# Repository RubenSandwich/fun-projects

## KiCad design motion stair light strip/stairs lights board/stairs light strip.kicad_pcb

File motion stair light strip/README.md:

## motion activated stair light strip

A simple, no IOT, motion activated stair light

## BOM

* 24v power supply
* [Sensky 6A DC 12V 24V PIR Motion Sensor](https://www.amazon.com/Sensky-Function-Control-Controller-Lighting/dp/B0B4K2Q7K9/ref=sr_1_23?crid=3AGQ66JBI1T4I&dib=eyJ2IjoiMSJ9.xUSOzHpblpoWn406B4-OBZFLz6d4soG2-rCj22BZ4TVwtl2oj7zBpFSsm9bGVf4_0vr2__NiO2qRjmIovLB6Cl-oex97yxg1mPl1SFR1d35Xbk69rIP4NijKcqR74HMDt8XPdo_WN_JfRDuOrUlUvaxq_QLUiuyCcHjCWXG1KOQzDuKs777sMJBGEr9q2cRSSDjf5W2F9OwXw6ElvNTGThpiMOUk_iMA_sRr2h6lEkTxdSnYWCXfyEl0XtqK0hp1d54DAIPvzWh6n2200xwKC1Srvh-nk0dEnyT1JrPJjKc.FILWEKSNVr479REpNQmRwOyHtakDh_g0QBcfDnpH2tw&dib_tag=se&keywords=motion%2Bactivated%2Bmodule&qid=1732066020&sprefix=motion%2Bactivated%2Bmodule%2Caps%2C201&sr=8-23&th=1)
* [Light strip](https://www.amazon.com/IKERY-Silicone-Waterproof-Decoration（Power-Included）/dp/B0B7RDBT89/ref=sr_1_22_sspa?crid=3Q7LC3KLRZKES&dib=eyJ2IjoiMSJ9.uvSizN30if3GPO9yVlsrHTzEI6fy9r3d7WXvXWqh24xlPGxJmMbmaGfHv6yVIscbHMaRuJwYZWzsTD4VyLnd_XchH1hdfdvzGfN6ygw8GdbzDVly5eUVatRmDDCMvimbZPNP77smsaMjOpAMJSRxJzvhMKM2c1lFD6wII6Rla-b9U_iaw8UnhKgI0-jkGeVBDfai_tf9VyhQNr9QWe5irDekJfC-4vslWlvkFwHpLkwcSbz8z0jpKv2qavOBq6ZJ_kBjVCgBb5g1EH9nqNobS5z9IcqmHWwf-ix6ov6u_Ew.ZNvmJLoxZ4x5pzZVM_lsjzTqeAHr9BF8dUG4B6t89TI&dib_tag=se&keywords=light%2Bstrip&qid=1732065987&sprefix=light%2Bstrip%2Caps%2C114&sr=8-22-spons&sp_csd=d2lkZ2V0TmFtZT1zcF9tdGY&th=1)
* [PWM Dimming Controller for LED Lights](https://www.amazon.com/dp/B07WSNXCGH/ref=sspa_dk_detail_2?psc=1&pd_rd_i=B07WSNXCGH&pd_rd_w=VHtDG&content-id=amzn1.sym.8c2f9165-8e93-42a1-8313-73d3809141a2&pf_rd_p=8c2f9165-8e93-42a1-8313-73d3809141a2&pf_rd_r=1DBQBTRBZEQT91KC1VM0&pd_rd_wg=0CCZs&pd_rd_r=8e70c9a4-7aac-4eac-b981-38a4b0e1649c&s=industrial&sp_csd=d2lkZ2V0TmFtZT1zcF9kZXRhaWw)
* For the circuit board
    * [Pluggable Terminal Blocks EURO BLOCK 4P](https://www.mouser.com/ProductDetail/737-EBWA-04-A)
    * [Pluggable Terminal Blocks EURO BLOCK 2P](https://www.mouser.com/ProductDetail/737-EBWA-02-A)
    * [SparkFun Accessories DC Barrel Power Jack/Connector](https://www.mouser.com/ProductDetail/474-PRT-00119)

MIT License

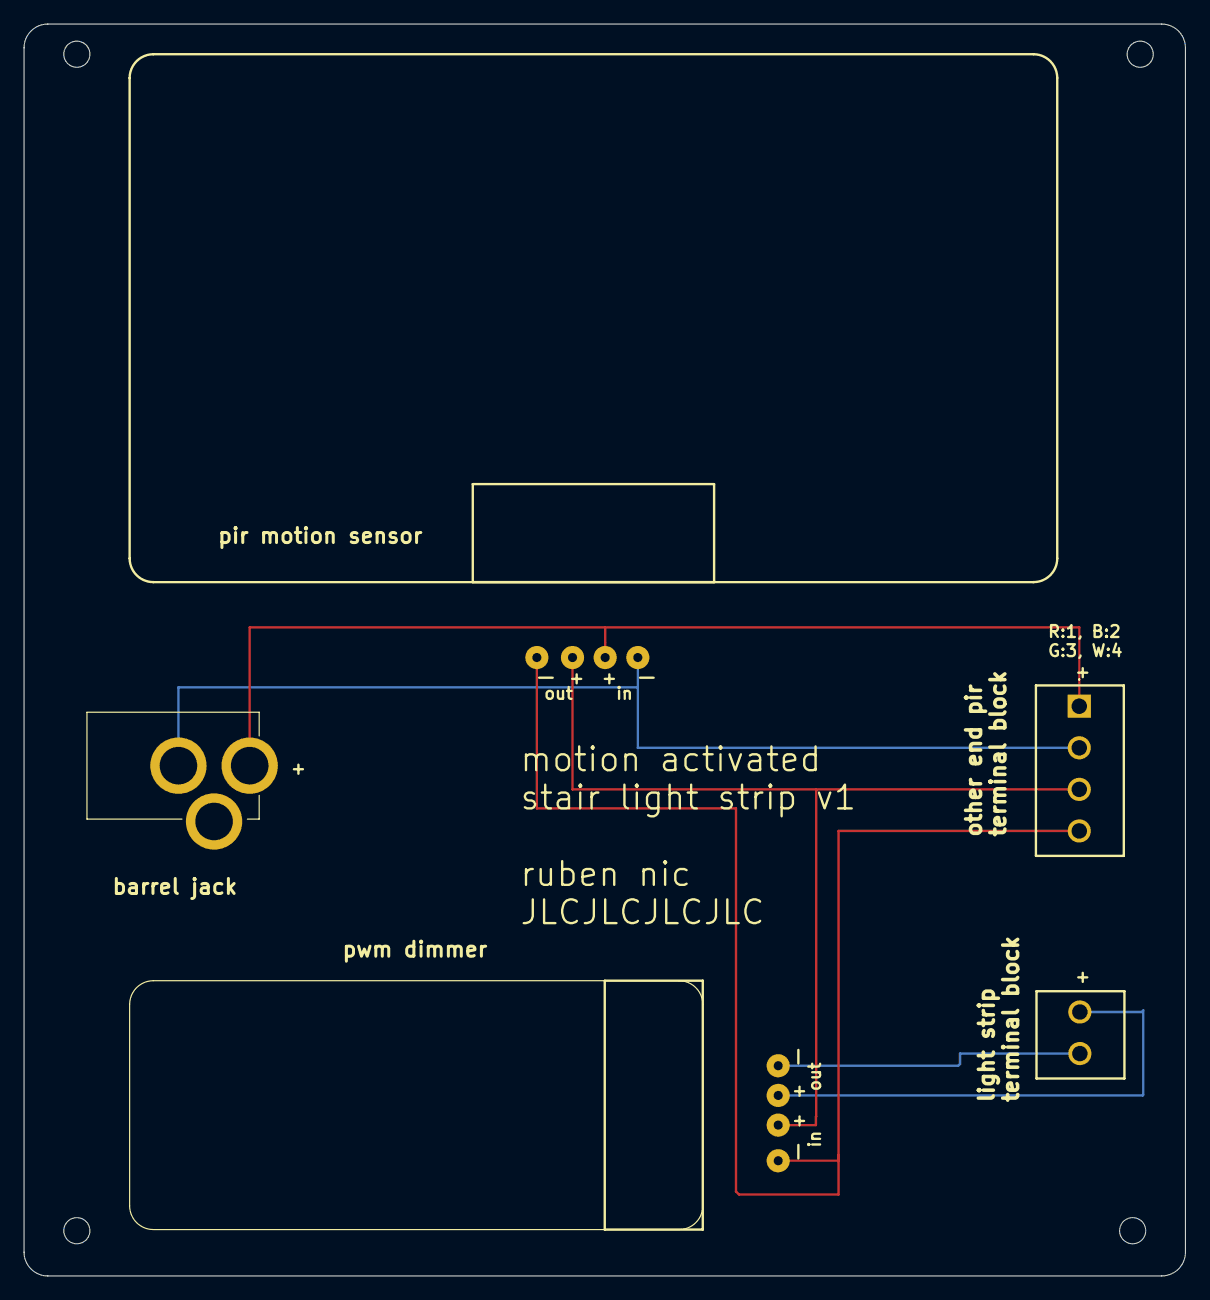
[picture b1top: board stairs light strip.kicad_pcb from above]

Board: 2 copper layers, 97.8 x 105.4 mm, 9 parts (0 on the bottom side), 6 nets.

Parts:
MH1, MH2, MH3, MH4: MountingHole_2.2mm_M2
barrel jack: PRT-00119; PRT00119
light strip terminal block: EBWA-02-A; EBWA02A
pir terminal block: EBWA-04-A; EBWA04A
pir-motion-sensor1: Conn_01x04_Socket; 4_through_holes
pwm-dimmer1: Conn_01x04_Socket; 4_through_holes

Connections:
unnamed: pir terminal block.4, pir-motion-sensor1.1, pwm-dimmer1.1
unnamed: pir terminal block.3, pir-motion-sensor1.2, pwm-dimmer1.2
unnamed: barrel jack.1, pir terminal block.1, pir-motion-sensor1.3
unnamed: barrel jack.2, pir terminal block.2, pir-motion-sensor1.4
unnamed: light strip terminal block.1, pwm-dimmer1.3
unnamed: light strip terminal block.2, pwm-dimmer1.4

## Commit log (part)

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2024-09-16 Add the start of the solar system clock project
2024-09-16 Add concertina project
2024-09-20 Add blackhole graphics of sucking in particles
2024-09-20 Add some basic error logging
2024-09-21 Dork around with using JS to "lock" orientation
2024-10-09 Have stars explode, and connect the suns cycles
2024-10-10 Turns out num separators are an es6 feature
2024-10-10 loading sounds and listening to it ending
2024-10-13 add the ability to add alt text to the canvas
2024-10-14 better organize the src code
2024-10-18 re organize
2024-10-20 numbers
2024-10-25 Have sun and nebulas "breath"
2024-10-28 Destroy extra canvases, and fix nebula alpha
2024-11-01 First try with it all together
2024-11-01 rename to end times
2024-11-01 update change intervals
2024-11-04 add celestial bodies in logical order
2024-11-07 Scaffolding
2024-11-07 first pass AI convert to TS
2024-11-07 Revert "first pass AI convert to TS"
    This reverts commit 4cbe09328da336d48529a94f5e2d8eff10b38e3d.
2024-11-08 finish TS
2024-11-09 do not create source maps for build
2024-11-09 clean up unneeded files
2024-11-09 Update src urls
2024-11-09 Add GHA to update solar system clock
2024-11-09 Move to a different path check
2024-11-09 Also allow for manual dispatch
2024-11-09 Give permission to trigger actions
2024-11-09 update perms
2024-11-09 Move to using a PAT
2024-11-09 test new GHA
2024-11-12 Clean up and use fetch
2024-11-16 Add a start screen
2024-11-17 use a parcel plugin to generate PWA manifest
2024-11-17 Update repository-dispatch action name
2024-11-17 Separate out the simple/initial universe
2024-11-17 Fix a bunch of type errors
2024-11-18 Add StarStage enum and make star grow to twinkle
2024-11-18 fade out the simple universe
2024-11-18 update pwa scope
2024-11-18 second attempt at a scope fix
2024-11-18 another attempt at a scope fix
2024-11-18 move to using css transitions
2024-11-18 Start on a big bang, and prevent nebula "pop in"
2024-11-19 iOS 9 doesn't like modern CSS
2024-11-20 Add a bunch of other projects
2024-11-20 Continue adding pictures and updating readmes
2024-11-20 Move all images to jpegs
2024-11-20 bunch more organizing
2024-11-20 Few more pictures that i forgot
2024-11-20 Update vibration module to use 100k resistor
2024-11-24 separate out the big bang universe
2024-11-24 Add a canvas description to the universes
2024-11-26 Add a nebula stage and clean up transition code
2024-12-05 python files to ignore
2024-12-06 Add sleep dimmer project
2024-12-09 Add the dimmer class and start writing the modes
2024-12-09 Get the breathing mode working
2024-12-09 Add in "sleep/wind down" mode
2024-12-09 Turn off when sleep is done and some cleanup
2024-12-09 More consistent naming
2024-12-09 Better specified class inits
2024-12-09 Start the dimmer off
2024-12-09 a few edge cases around strange dimmer behavior
2024-12-09 Have the potentiometer map to only working values
2024-12-11 Clean up PWM code
2024-12-19 Add directions on setting up a sshfs
2024-12-19 Add basic information about the sleep dimmer
2024-12-19 Clean up a bunch of code and turn off unused timer
2024-12-19 Implement turning off the zeroCrossoverPin irq
2024-12-19 Move the dimmer value back to 0-1.0
2024-12-19 Turn off the button irq when off
2024-12-19 Fix a bug in nebula changed logic
2025-01-03 Add a speed modifier and log times
2025-01-21 Add second screen mirror project
2025-12-18 start adding the ability to save state to JSON
2025-12-19 Finish writing toJSON for celestial_bodies
2025-12-21 add todo printer experiments
2025-12-21 add basic fromJSON, not tested yet
2025-12-21 Add basic state JSON modal
2025-12-21 Wire up the buttons for loading state
2025-12-21 Move star exploded callback to use an event
2025-12-21 Move big bang callback to using events
2025-12-21 Save all of of universeState
2025-12-25 Attempt at loading back state
2025-12-27 finish loading state code
2025-12-28 clean up popover handling code
2025-12-28 rename cbType
2026-01-04 remove tick internal code and base it on frames
2026-01-30 Move change internal functions out of constants
2026-02-15 Fix sun in simple universe
2026-05-26 Add in the debug states loading
2026-05-26 move away from more constants
2026-05-26 Fix heading styles of state loading popover
2026-05-26 Remove some completed todos
